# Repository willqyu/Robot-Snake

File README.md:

## Robot Snake
Firmware for modular robotic snake, as designed and built for the MET IIA Major Project 2024. 
Team: William Y, Piers B, Catherine L, Nick N

## Module Design
Servo-actuated cables for 2DoF per module.
<br><br>

Custom PCBs designed for each module, comm over I2C, Pi Pico as slave.
<br>
<br>

Head uses Pi Zero with PiCam v2 and Neopixel Ring

## Gallery

## Schematics

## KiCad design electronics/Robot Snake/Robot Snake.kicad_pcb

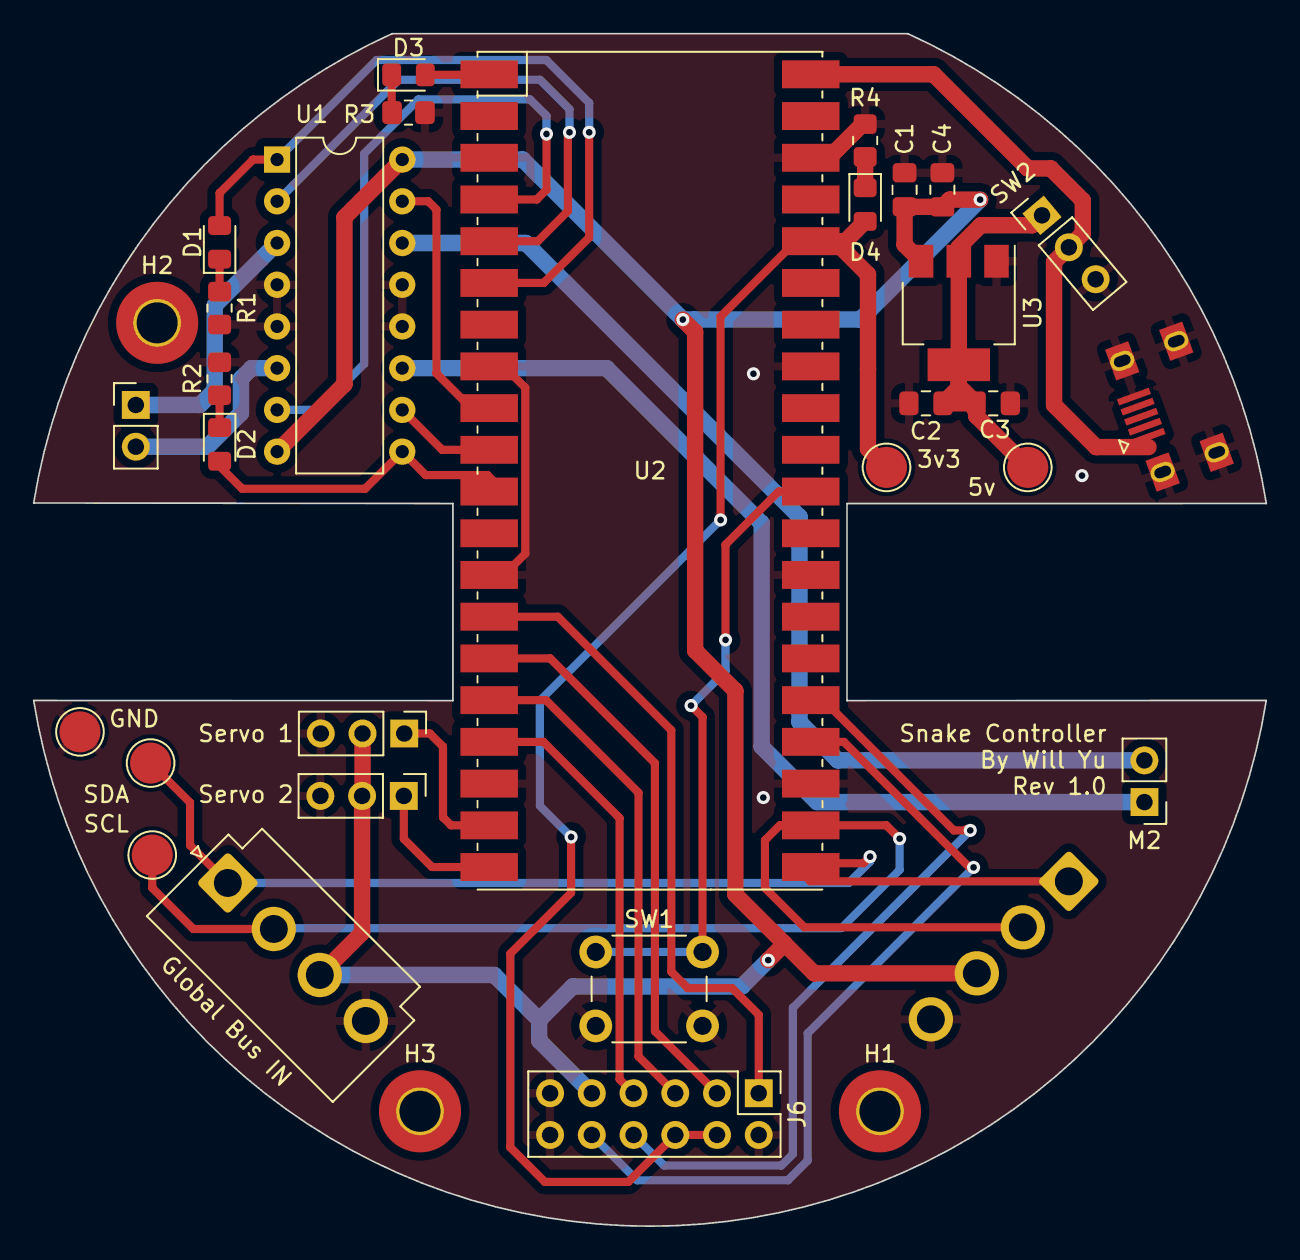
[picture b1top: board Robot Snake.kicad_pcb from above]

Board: 2 copper layers, 75.0 x 72.6 mm, 33 parts (1 on the bottom side), 31 nets.

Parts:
3v3: 3v3; TestPoint_Pad_D2.5mm
5v: Bat; TestPoint_Pad_D2.5mm
C1, C2: 10uF; C_0805_2012Metric_Pad1.18x1.45mm_HandSolder
C3, C4: 0.1nF; C_0805_2012Metric_Pad1.18x1.45mm_HandSolder
D1, D2, D3, D4: LED; LED_0805_2012Metric_Pad1.15x1.40mm_HandSolder
GND: GND; TestPoint_Pad_D2.5mm
Global Bus IN: Global Bus IN; JST_VH_B4P-VH_1x04_P3.96mm_Vertical
Global Bus OUT: Global Bus OUT; JST_VH_B4P-VH_1x04_P3.96mm_Vertical
H1, H2, H3: MountingHole; MountingHole_2.5mm_Pad_TopBottom
J5: USB_B_Micro; MicroUSB
J6: Conn_02x06_Odd_Even; PinHeader_2x06_P2.54mm_Vertical
M1, M2: Motor_DC; PinHeader_1x02_P2.54mm_Vertical
R1, R2, R3, R4: 15; R_0805_2012Metric_Pad1.20x1.40mm_HandSolder
SCL: SCL; TestPoint_Pad_D2.5mm
SDA: SDA; TestPoint_Pad_D2.5mm
SW1: SW_Push; SW_PUSH_6mm
SW2: SW_SPDT; PinHeader_1x03_P2.54mm_Vertical
Servo 1: Servo 1; PinHeader_1x03_P2.54mm_Vertical
Servo 2: Servo 2; PinHeader_1x03_P2.54mm_Vertical
U1: L293D; DIP-16_W7.62mm
U2: Pico; RPi_Pico_SMD no debug
U3: AMS1117-5.0; SOT-223-3_TabPin2

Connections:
+3V3: 3v3.1, D4.2 (A), J6.4, J6.6, U2.36 (3V3)
+5V: 5v.1, C2.1, C3.1, SW2.1 (A), U3.2 (VO)
/GPIO10: J6.1, U2.14 (GPIO10)
/GPIO11: J6.3, U2.15 (GPIO11)
/GPIO12: J6.5, U2.16 (GPIO12)
/GPIO13: J6.7, U2.17 (GPIO13)
/Motor 1 EN: D1.2 (A), U1.1 (EN1,2), U2.6 (GPIO4)
/Motor 1 a: U1.2 (1A), U2.5 (GPIO3)
/Motor 1 b: U1.7 (2A), U2.4 (GPIO2)
/Motor 2 EN: D2.2 (A), U1.9 (EN3,4), U2.11 (GPIO8)
/Motor 2 a: U1.10 (3A), U2.10 (GPIO7)
/Motor 2 b: U1.15 (4A), U2.9 (GPIO6)
/SCL: Global Bus IN.2, Global Bus OUT.2, SCL.1, U2.22 (GPIO17)
/SCL int: J6.8, U2.25 (GPIO19)
/SDA: Global Bus IN.1, Global Bus OUT.1, SDA.1, U2.21 (GPIO16)
/SDA int: J6.10, U2.24 (GPIO18)
/Servo 1: Servo 1.1, U2.19 (GPIO14)
/Servo 2: Servo 2.1, U2.20 (GPIO15)
/USB IN: J5.1 (VBUS), SW2.2 (B), U2.40 (VBUS)
GND: C1.2, C2.2, C3.2, C4.2, GND.1, Global Bus IN.4, Global Bus OUT.4, J5.5 (GND), J5.6 (Shield), J6.2, J6.11, J6.12, R1.2, R2.2, R3.2, R4.2, SW1.2, SW2.3 (C), Servo 1.3, Servo 2.3, U1.4 (GND), U1.5 (GND), U1.12 (GND), U1.13 (GND), U2.3 (GND), U2.8 (GND), U2.13 (GND), U2.18 (GND), U2.23 (GND), U2.28 (GND), U2.33 (AGND), U2.38 (GND), U3.1 (GND)
unnamed: D1.1 (K), R1.1
unnamed: D2.1 (K), R2.1
unnamed: D3.2 (A), U2.1 (GPIO0)
unnamed: D3.1 (K), R3.1
unnamed: D4.1 (K), R4.1
unnamed: M1.1 (+), U1.3 (1Y)
unnamed: M1.2 (-), U1.6 (2Y)
unnamed: M2.1 (+), U1.11 (3Y)
unnamed: M2.2 (-), U1.14 (4Y)
unnamed: SW1.1, U2.30 (RUN)
VCC: C1.1, C4.1, Global Bus IN.3, Global Bus OUT.3, J6.9, Servo 1.2, Servo 2.2, U1.8 (VCC2), U1.16 (VCC1), U3.3 (VI)

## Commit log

2024-05-09 Initial
2024-05-25 PCB + motors
2024-05-25 servo
2024-05-28 Moving
2024-08-11 Updated main
2024-08-26 Update README.md
    Added pics
